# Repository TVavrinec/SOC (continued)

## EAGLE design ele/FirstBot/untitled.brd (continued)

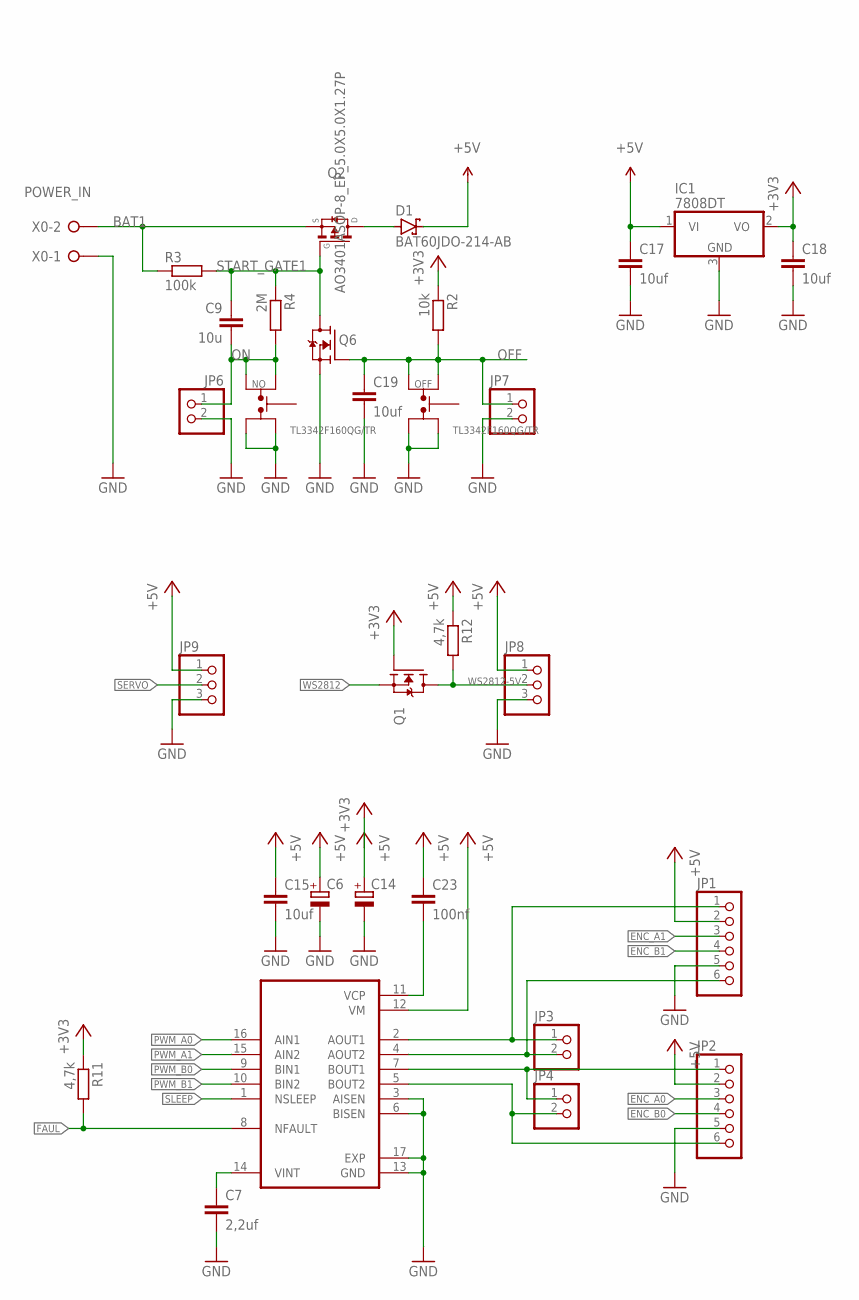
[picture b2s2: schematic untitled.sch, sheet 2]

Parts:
C6, C14: CPOL-EUSANYO_SMD_F8; SANYO-OSCON_SMD_F8
C7: 2,2uf; C0402K
C9: 10u; C0402K
C15, C17, C18: 10uf; C0603
C19: 10uf; C0402K
C23: 100nf; C0402K
D1: BAT60JDO-214-AB; DO214BA
IC1: 7808DT; TO252
JP1, JP2: PINHD-1X6; 1X06
JP3, JP4, JP6, JP7: PINHD-1X2; 1X02
JP8, JP9: PINHD-1X3; 1X03
NO: TL3342F160QG/TR
OFF: TL3342F160QG/TR
Q1, Q6: N-MOSFET-SOT23-GSD; SOT23
Q2: AO3401ASOP-8_EP_5.0X5.0X1.27P; SOP-8_EP_5.0X5.0X1.27P
R2: 10k; R0402
R3: 100k; R0402
R4: 2M; R0402
R11, R12: 4,7k; R0402
U$9: DRV8833CPWPR; SOP65P640X120-17N
X0: POWER_IN; W237-132

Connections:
+3V3: C18.1, IC1.2 (VO), Q1.1 (G), R2.1, R11.1; also elsewhere on the board
+5V: C6.+, C14.+, C15.1, C17.1, C23.2, D1.C, IC1.1 (VI), JP1.2, JP2.2, JP8.1, JP9.1, R12.1, U$9.12 (VM)
BAT1: Q2.1 (S), Q2.2 (S), Q2.3 (S), R3.1, X0.2
ENC_A0: JP2.3; also elsewhere on the board
ENC_A1: JP1.3; also elsewhere on the board
ENC_B0: JP2.4; also elsewhere on the board
ENC_B1: JP1.4; also elsewhere on the board
FAUL: R11.2, U$9.8 (NFAULT); also elsewhere on the board
GND: C6.-, C7.2, C14.-, C15.2, C17.2, C18.2, C19.2, IC1.3 (GND), JP1.5, JP2.5, JP6.2, JP7.2, JP8.3, JP9.3, NO.1, NO.2, OFF.1, OFF.2, Q6.2 (S), U$9.3 (AISEN), U$9.6 (BISEN), U$9.13 (GND), U$9.17 (EXP), X0.1; also elsewhere on the board
unnamed: JP1.1, JP3.1, U$9.2 (AOUT1)
unnamed: D1.A, Q2.5 (D), Q2.6 (D), Q2.7 (D), Q2.8 (D), Q2.9 (D)
unnamed: C23.1, U$9.11 (VCP)
unnamed: JP1.6, JP3.2, U$9.4 (AOUT2)
unnamed: JP2.1, JP4.1, U$9.7 (BOUT1)
unnamed: JP2.6, JP4.2, U$9.5 (BOUT2)
unnamed: C7.1, U$9.14 (VINT)
OFF: C19.1, JP7.1, OFF.3, OFF.4, Q6.1 (G), R2.2
ON: C9.2, JP6.1, NO.3, NO.4, R4.2
PWM_A0: U$9.16 (AIN1); also elsewhere on the board
PWM_A1: U$9.15 (AIN2); also elsewhere on the board
PWM_B0: U$9.9 (BIN1); also elsewhere on the board
PWM_B1: U$9.10 (BIN2); also elsewhere on the board
SERVO: JP9.2; also elsewhere on the board
SLEEP: U$9.1 (NSLEEP); also elsewhere on the board
START_GATE1: C9.1, Q2.4 (G), Q6.3 (D), R3.2, R4.1
WS2812: Q1.2 (S); also elsewhere on the board
WS2812-5V: JP8.2, Q1.3 (D), R12.2

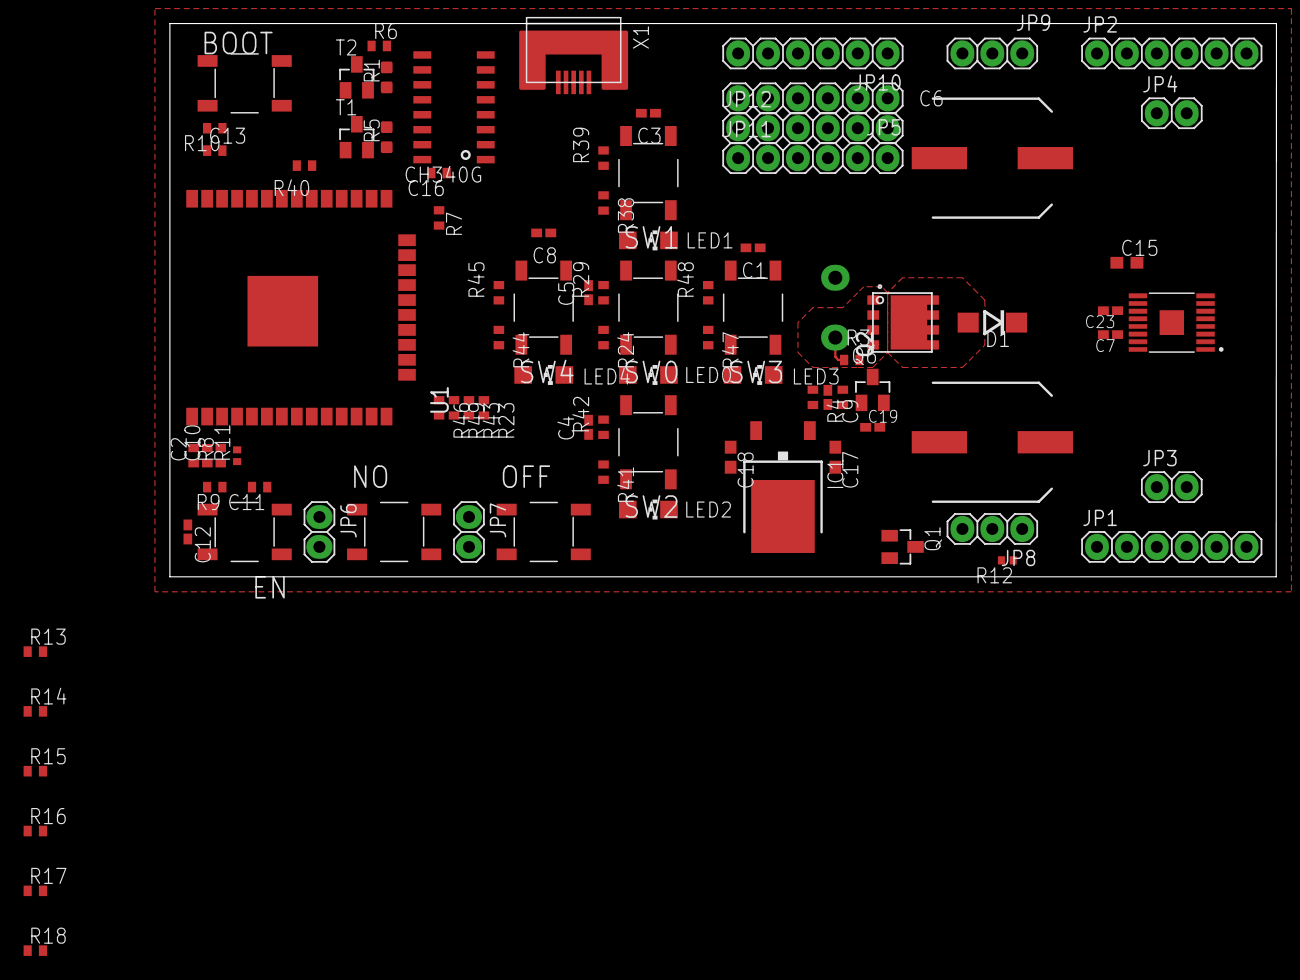
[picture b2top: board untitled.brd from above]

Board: 2 copper layers, 94.0 x 47.0 mm, 91 parts (1 on the bottom side), 61 nets.

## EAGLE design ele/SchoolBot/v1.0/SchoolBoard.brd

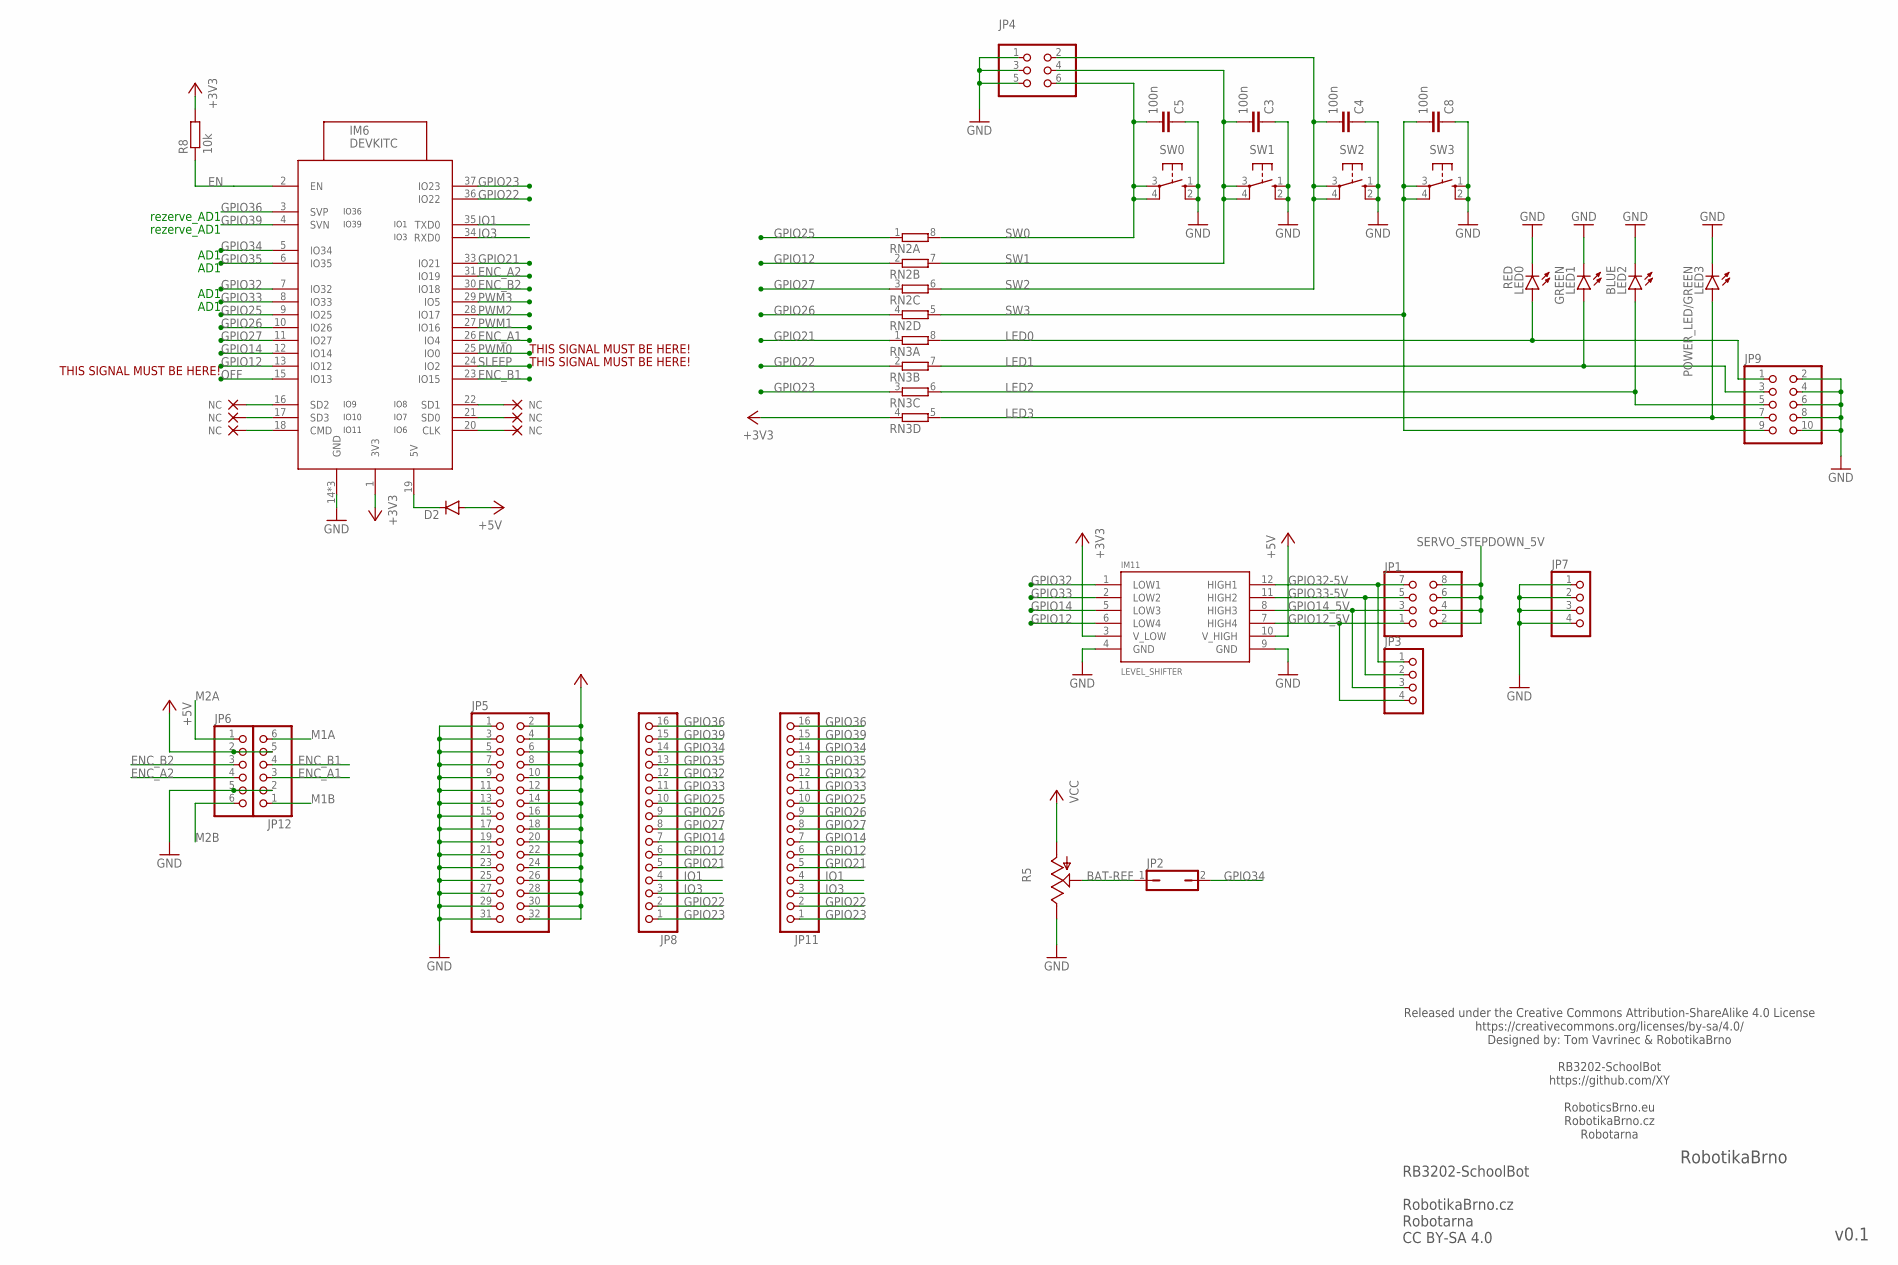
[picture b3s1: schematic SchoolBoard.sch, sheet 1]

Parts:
C3, C4, C5, C8: 100n; C1206
D2: DIODE-D-7.5; D-7.5
IM6: DEVKITC
IM11: LEVEL_SHIFTER
JP1: PINHD-2X4; 2X04
JP2: JP1Q; JP1
JP3, JP7: PINHD-1X4; 1X04
JP4: PINHD-2X3; 2X03
JP5: PINHD-2X16; 2X16
JP6, JP12: PINHD-1X6; 1X06
JP8, JP11: PINHD-1X16; 1X16
JP9: PINHD-2X5; 2X05
LED0: RED; LED3MM
LED1: GREEN; LED3MM
LED2: BLUE; LED3MM
LED3: POWER_LED/GREEN; LED3MM
R5: TRIM_US-SM-42/43X; SM-42/43X
R8: 10k; R0805
RN2, RN3: 4R-NEXBS8V; EXBS8V
SW0, SW1, SW2, SW3: 10-XX; B3F-10XX

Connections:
+3V3: IM6.1 (3V3), IM11.3 (V_LOW), JP5.2, JP5.4, JP5.6, JP5.8, JP5.10, JP5.12, JP5.14, JP5.16, JP5.18, JP5.20, JP5.22, JP5.24, JP5.26, JP5.28, JP5.30, JP5.32, R8.2, RN3.4 (1); also elsewhere on the board
+5V: D2.A, IM11.10 (V_HIGH), JP6.2, JP12.5; also elsewhere on the board
+5V_ESP: D2.C, IM6.19 (5V)
BAT-REF: JP2.1, R5.2 (S)
EN: IM6.2 (EN), R8.1; also elsewhere on the board
ENC_A1: IM6.26 (IO4), JP12.3
ENC_A2: IM6.31 (IO19), JP6.4
ENC_B1: IM6.23 (IO15), JP12.4
ENC_B2: IM6.30 (IO18), JP6.3
GND: C3.1, C4.1, C5.1, C8.1, IM6.14 (GND), IM6.32 (GND), IM6.38 (GND), IM11.4 (GND), IM11.9 (GND), JP4.1, JP4.3, JP4.5, JP5.1, JP5.3, JP5.5, JP5.7, JP5.9, JP5.11, JP5.13, JP5.15, JP5.17, JP5.19, JP5.21, JP5.23, JP5.25, JP5.27, JP5.29, JP5.31, JP6.5, JP7.1, JP7.2, JP7.3, JP7.4, JP9.2, JP9.4, JP9.6, JP9.8, JP9.10, JP12.2, LED0.K (C), LED1.K (C), LED2.K (C), LED3.K (C), R5.3 (E), SW0.1 (S), SW0.2 (S1), SW1.1 (S), SW1.2 (S1), SW2.1 (S), SW2.2 (S1), SW3.1 (S), SW3.2 (S1); also elsewhere on the board
GPIO12: IM6.13 (IO12), IM11.6 (LOW4), JP8.6, JP11.6, RN2.2 (1)
GPIO12_5V: IM11.7 (HIGH4), JP1.1, JP3.4
GPIO14: IM6.12 (IO14), IM11.5 (LOW3), JP8.7, JP11.7
GPIO14_5V: IM11.8 (HIGH3), JP1.3, JP3.3
GPIO21: IM6.33 (IO21), JP8.5, JP11.5, RN3.1
GPIO22: IM6.36 (IO22), JP8.2, JP11.2, RN3.2 (1)
GPIO23: IM6.37 (IO23), JP8.1, JP11.1, RN3.3 (1)
GPIO25: IM6.9 (IO25), JP8.10, JP11.10, RN2.1
GPIO26: IM6.10 (IO26), JP8.9, JP11.9, RN2.4 (1)
GPIO27: IM6.11 (IO27), JP8.8, JP11.8, RN2.3 (1)
GPIO32: IM6.7 (IO32), IM11.1 (LOW1), JP8.12, JP11.12
GPIO32-5V: IM11.12 (HIGH1), JP1.7, JP3.1
GPIO33: IM6.8 (IO33), IM11.2 (LOW2), JP8.11, JP11.11
GPIO33-5V: IM11.11 (HIGH2), JP1.5, JP3.2
GPIO34: IM6.5 (IO34), JP2.2, JP8.14, JP11.14
GPIO35: IM6.6 (IO35), JP8.13, JP11.13; also elsewhere on the board
GPIO36: IM6.3 (SVP), JP8.16, JP11.16
GPIO39: IM6.4 (SVN), JP8.15, JP11.15
IO1: IM6.35 (TXD0), JP8.4, JP11.4
IO3: IM6.34 (RXD0), JP8.3, JP11.3
IO9_NC: IM6.16 (SD2)
IO9_NC1: IM6.20 (CLK)
IO10_NC: IM6.17 (SD3)
IO10_NC1: IM6.21 (SD0)
IO11_NC: IM6.18 (CMD)
IO11_NC1: IM6.22 (SD1)
LED0: JP9.1, LED0.A, RN3.8 (2)
LED1: JP9.3, LED1.A, RN3.7 (2)
LED2: JP9.5, LED2.A, RN3.6 (2)
LED3: JP9.7, LED3.A, RN3.5 (2)
M1A: JP12.6; also elsewhere on the board
M1B: JP12.1; also elsewhere on the board
M2A: JP6.1; also elsewhere on the board
M2B: JP6.6; also elsewhere on the board
OFF: IM6.15 (IO13); also elsewhere on the board
PWM0: IM6.25 (IO0); also elsewhere on the board
PWM1: IM6.27 (IO16); also elsewhere on the board
PWM2: IM6.28 (IO17); also elsewhere on the board
PWM3: IM6.29 (IO5); also elsewhere on the board
SERVO_STEPDOWN_5V: JP1.2, JP1.4, JP1.6, JP1.8; also elsewhere on the board
SLEEP: IM6.24 (IO2); also elsewhere on the board
SW0: C5.2, JP4.6, RN2.8 (2), SW0.3, SW0.4 (P1)
SW1: C3.2, JP4.4, RN2.7 (2), SW1.3, SW1.4 (P1)
SW2: C4.2, JP4.2, RN2.6 (2), SW2.3, SW2.4 (P1)
SW3: C8.2, JP9.9, RN2.5 (2), SW3.3, SW3.4 (P1)
VCC: R5.1 (A); also elsewhere on the board

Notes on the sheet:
AD1
rezerve_AD1
RB3202-SchoolBot RobotikaBrno.cz Robotarna CC BY-SA 4.0
RobotikaBrno
v0.1
Released under the Creative Commons Attribution-ShareAlike 4.0 License https://creativecommons.org/licenses/by-sa/4.0/ Designed by: Tom Vavrinec & RobotikaBrno RB3202-SchoolBot https://github.com/XY RoboticsBrno.eu RobotikaBrno.cz Robotarna
THIS SIGNAL MUST BE HERE!

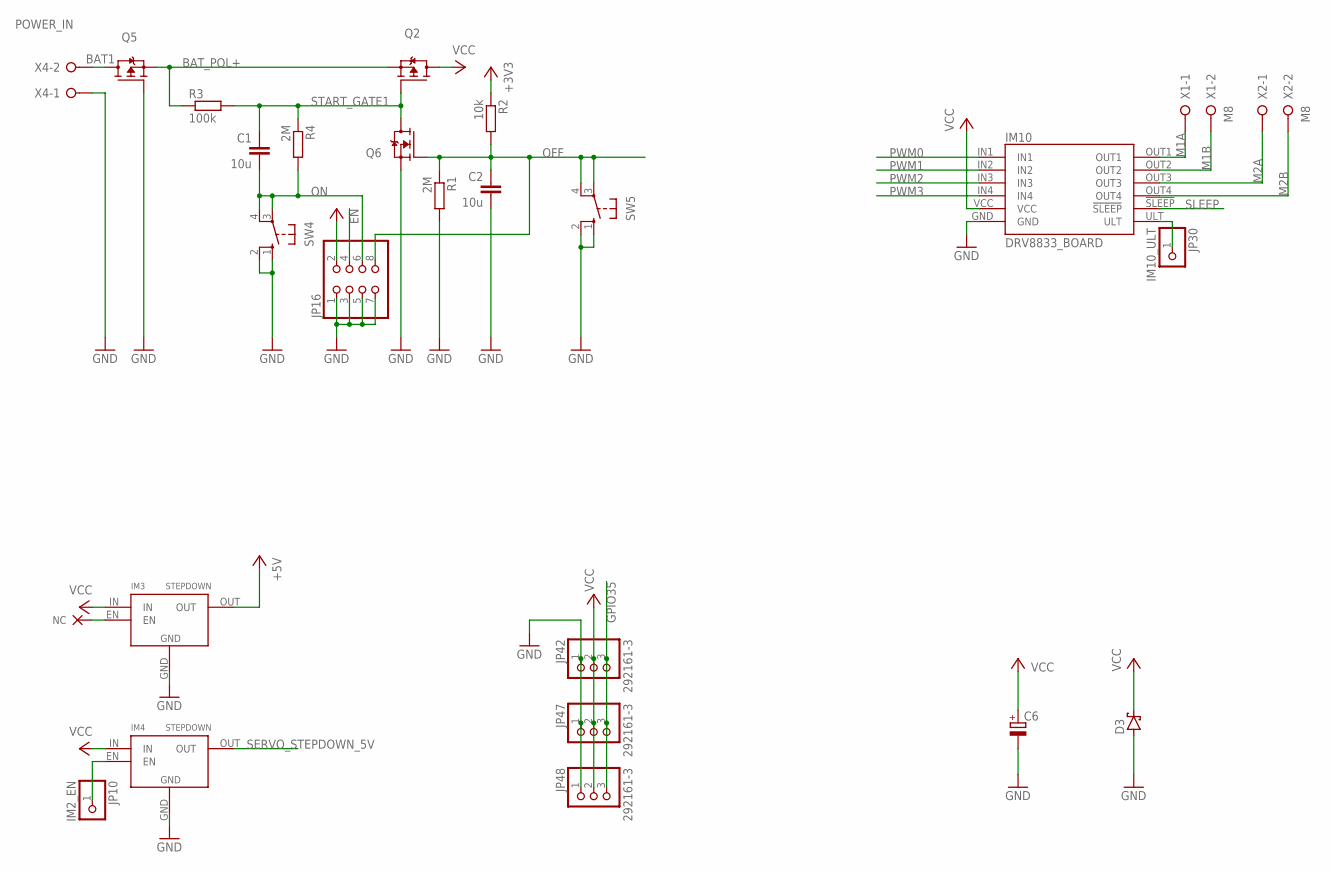
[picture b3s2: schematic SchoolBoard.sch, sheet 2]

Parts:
C1, C2: 10u; C1206
C6: CPOL-EUE5-10.5; E5-10,5
D3: SCHOTTKY-DIODEF126Z12; F126Z12
IM3, IM4: STEPDOWN
IM10: DRV8833_BOARD; PINHEAD
JP10: IM2_EN; 1X01
JP16: PINHD-2X4; 2X04
JP30: IM10_ULT; 1X01
JP42, JP47, JP48: 292161-3
Q2, Q5: P-MOSFET-TO220V; TO220V
Q6: N-MOSFET-SOT23-GSD; SOT23
R1: 2M; R0805
R2: 10k; R0805
R3: 100k; R0805
R4: 2M; M0805
SW4, SW5: 10-XX; B3F-10XX
X1, X2: M8; W237-132
X4: POWER_IN; W237-132

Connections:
+3V3: R2.1; also elsewhere on the board
+5V: IM3.OUT, JP16.2; also elsewhere on the board
BAT1: Q5.2 (D), X4.2
BAT_POL+: Q2.3 (S), Q5.3 (S), R3.1
EN: JP16.4; also elsewhere on the board
GND: C2.2, C6.-, D3.A, IM3.GND, IM4.GND, IM10.GND, JP16.1, JP16.3, JP16.5, JP16.7, JP42.1, JP47.1, JP48.1, Q5.1 (G), Q6.2 (S), R1.2, SW4.1 (S), SW4.2 (S1), SW5.1 (S), SW5.2 (S1), X4.1; also elsewhere on the board
GPIO35: JP42.3, JP47.3, JP48.3; also elsewhere on the board
IO9_NC2: IM3.EN
M1A: IM10.OUT1, X1.1; also elsewhere on the board
M1B: IM10.OUT2, X1.2; also elsewhere on the board
M2A: IM10.OUT3, X2.1; also elsewhere on the board
M2B: IM10.OUT4, X2.2; also elsewhere on the board
unnamed: IM10.ULT, JP30.1
OFF: C2.1, JP16.8, Q6.1 (G), R1.1, R2.2, SW5.3, SW5.4 (P1); also elsewhere on the board
ON: C1.2, JP16.6, R4.2, SW4.3, SW4.4 (P1)
PWM0: IM10.IN1; also elsewhere on the board
PWM1: IM10.IN2; also elsewhere on the board
PWM2: IM10.IN3; also elsewhere on the board
PWM3: IM10.IN4; also elsewhere on the board
SERVO_STEPDOWN_5V: IM4.OUT; also elsewhere on the board
SLEEP: IM10.!SLEEP; also elsewhere on the board
START_GATE1: C1.1, Q2.1 (G), Q6.3 (D), R3.2, R4.1
STEP2_EN1: IM4.EN, JP10.1
VCC: C6.+, D3.C, IM3.IN, IM4.IN, IM10.VCC, JP42.2, JP47.2, JP48.2, Q2.2 (D); also elsewhere on the board

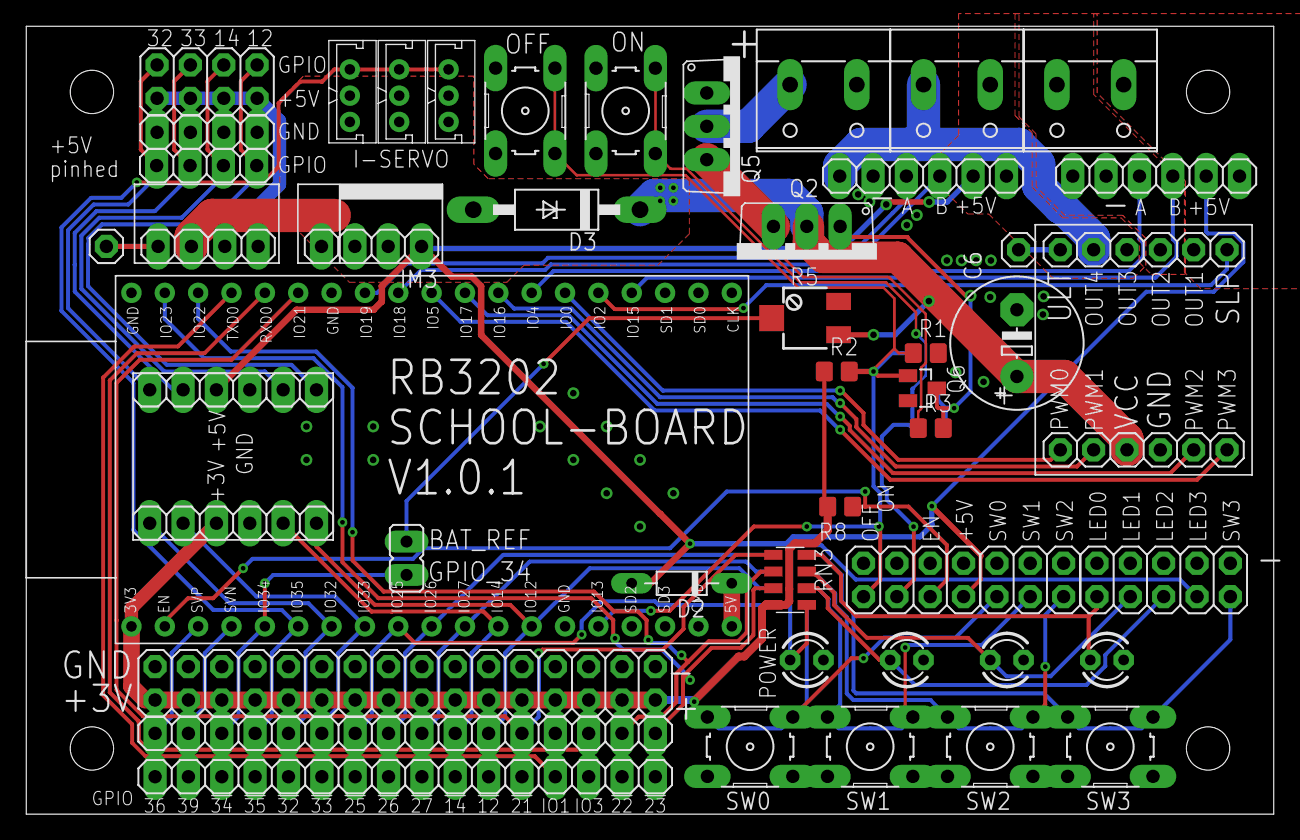
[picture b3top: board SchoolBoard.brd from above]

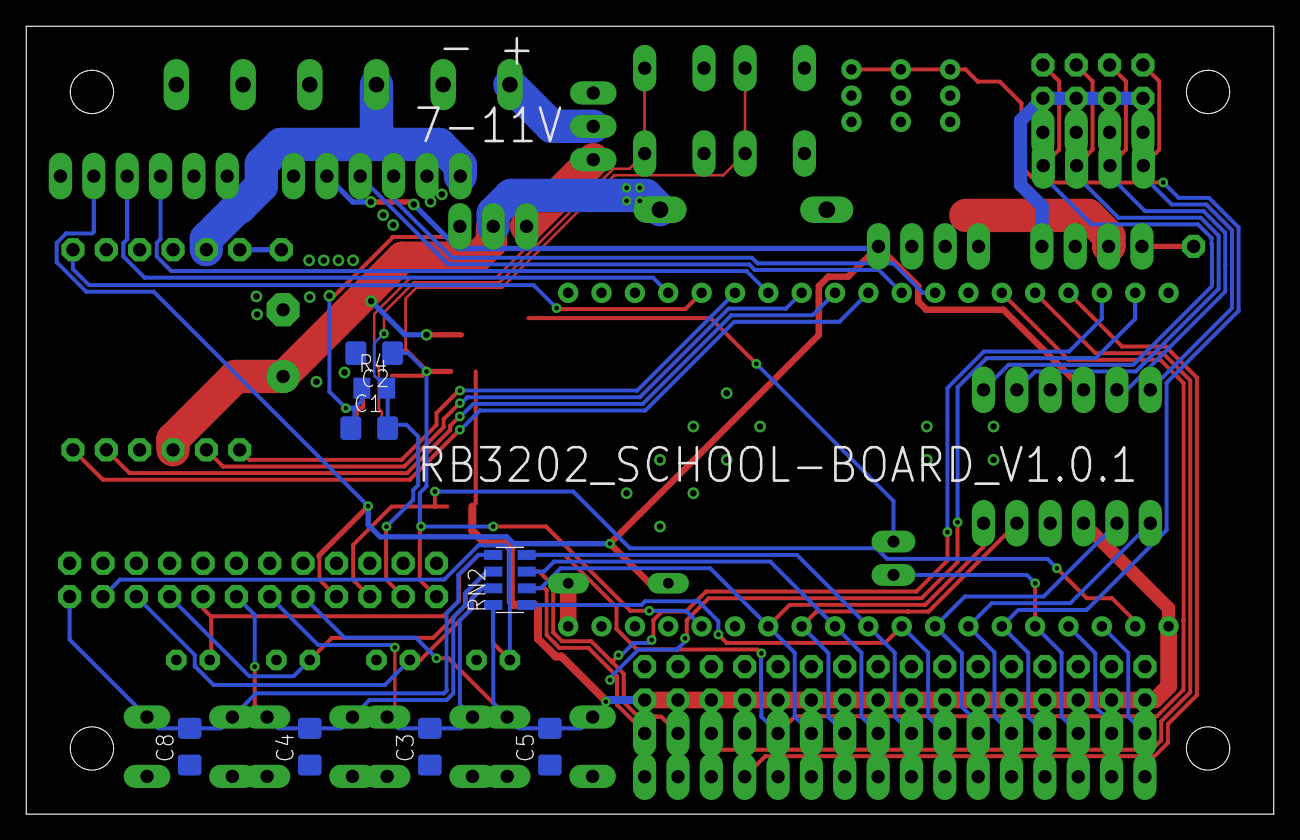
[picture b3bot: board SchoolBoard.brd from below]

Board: 2 copper layers, 95.0 x 60.0 mm, 55 parts (8 on the bottom side), 56 nets.

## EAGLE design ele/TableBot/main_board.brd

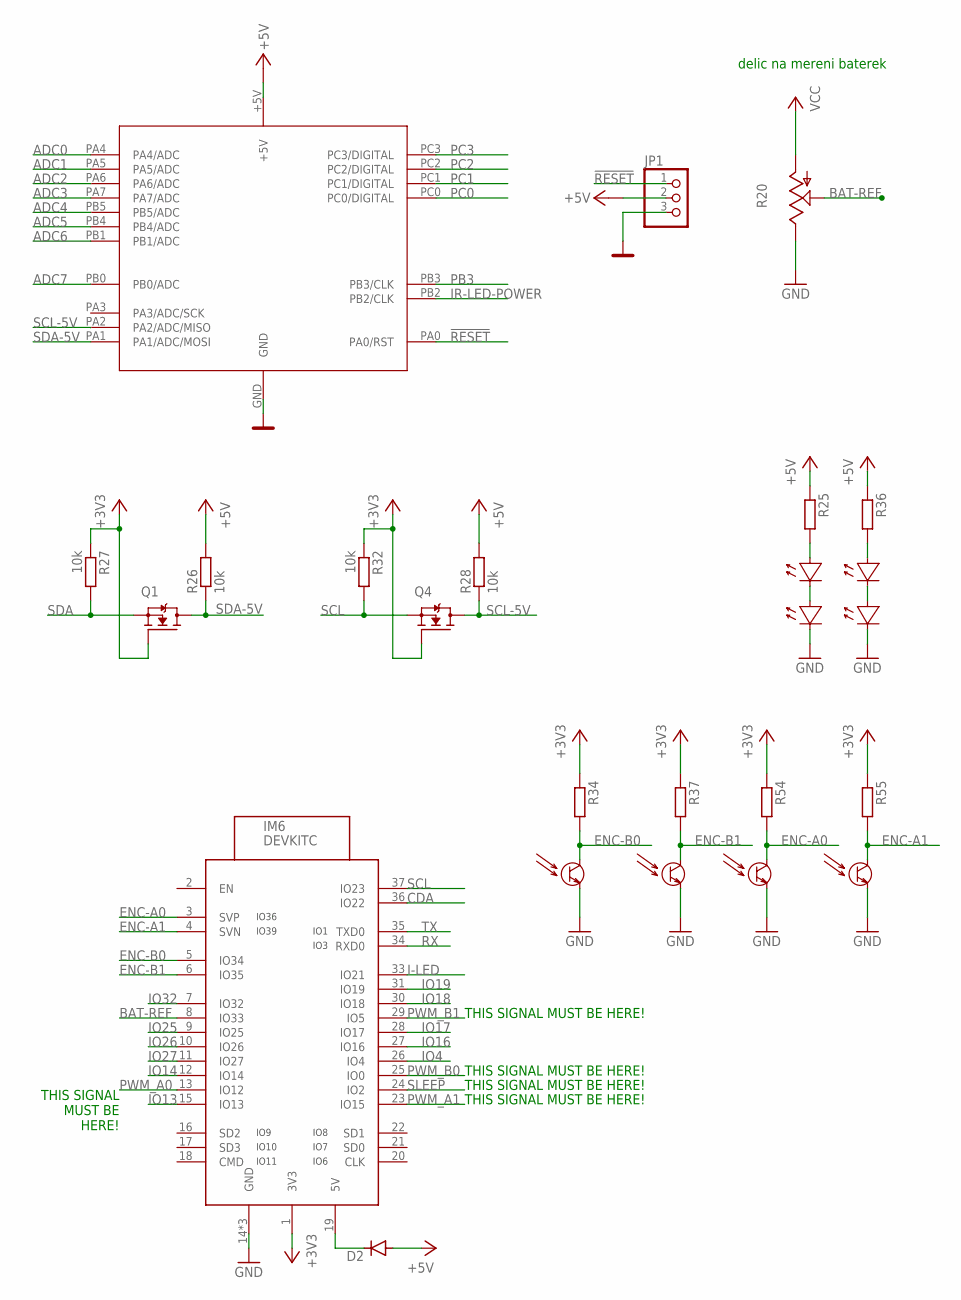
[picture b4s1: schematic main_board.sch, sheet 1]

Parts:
D2: DIODE-D-7.5; D-7.5
IM6: DEVKITC
JP1: PINHD-1X3; 1X03
Q1, Q4: N-MOSFET-SOT23-DIST; SOT23_DIST
R20: TRIM_US-SM-42/43X; SM-42/43X
R25, R34, R36, R37, R54, R55: R-EU_R0603; R0603
R26, R27, R28, R32: 10k; R0402
U$8: ATTINI1616SOIC; ATTINY1616-SOIC
U$11, U$15, U$16, U$20: BIR-NM13C1
U$13, U$21, U$22, U$23: L-NP-3C1

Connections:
!RESET: JP1.1, U$8.PA0 (PA0/RST)
+3V3: IM6.1 (3V3), Q1.1 (G), Q4.1 (G), R27.1, R32.1, R34.1, R37.1, R54.1, R55.1; also elsewhere on the board
+5V: D2.A, JP1.2, R25.1, R26.2, R28.2, R36.1, U$8.+5V; also elsewhere on the board
+5V_ESP: D2.C, IM6.19 (5V)
ADC0: U$8.PA4 (PA4/ADC); also elsewhere on the board
ADC1: U$8.PA5 (PA5/ADC); also elsewhere on the board
ADC2: U$8.PA6 (PA6/ADC); also elsewhere on the board
ADC3: U$8.PA7 (PA7/ADC); also elsewhere on the board
ADC4: U$8.PB5 (PB5/ADC); also elsewhere on the board
ADC5: U$8.PB4 (PB4/ADC); also elsewhere on the board
ADC6: U$8.PB1 (PB1/ADC); also elsewhere on the board
ADC7: U$8.PB0 (PB0/ADC)
BAT-REF: IM6.8 (IO33), R20.2 (S)
CDA: IM6.36 (IO22)
ENC-A0: IM6.3 (SVP), R54.2, U$22.PIN
ENC-A1: IM6.4 (SVN), R55.2, U$23.PIN
ENC-B0: IM6.5 (IO34), R34.2, U$13.PIN
ENC-B1: IM6.6 (IO35), R37.2, U$21.PIN
GND: IM6.14 (GND), IM6.32 (GND), IM6.38 (GND), JP1.3, R20.3 (E), U$8.GND, U$11.GND, U$13.GND, U$20.GND, U$21.GND, U$22.GND, U$23.GND; also elsewhere on the board
I-LED: IM6.33 (IO21); also elsewhere on the board
IO4: IM6.26 (IO4); also elsewhere on the board
IO13: IM6.15 (IO13); also elsewhere on the board
IO14: IM6.12 (IO14); also elsewhere on the board
IO16: IM6.27 (IO16); also elsewhere on the board
IO17: IM6.28 (IO17); also elsewhere on the board
IO18: IM6.30 (IO18); also elsewhere on the board
IO19: IM6.31 (IO19); also elsewhere on the board
IO25: IM6.9 (IO25); also elsewhere on the board
IO26: IM6.10 (IO26); also elsewhere on the board
IO27: IM6.11 (IO27); also elsewhere on the board
IO32: IM6.7 (IO32); also elsewhere on the board
IR-LED-POWER: U$8.PB2 (PB2/CLK); also elsewhere on the board
unnamed: R25.2, U$16.PIN (VCC)
unnamed: U$11.PIN (VCC), U$16.GND
unnamed: R36.2, U$15.PIN (VCC)
unnamed: U$15.GND, U$20.PIN (VCC)
PB3: U$8.PB3 (PB3/CLK); also elsewhere on the board
PC0: U$8.PC0 (PC0/DIGITAL); also elsewhere on the board
PC1: U$8.PC1 (PC1/DIGITAL); also elsewhere on the board
PC2: U$8.PC2 (PC2/DIGITAL); also elsewhere on the board
PC3: U$8.PC3 (PC3/DIGITAL)
PWM_A0: IM6.13 (IO12); also elsewhere on the board
PWM_A1: IM6.23 (IO15); also elsewhere on the board
PWM_B0: IM6.25 (IO0); also elsewhere on the board
PWM_B1: IM6.29 (IO5); also elsewhere on the board
RX: IM6.34 (RXD0); also elsewhere on the board
SCL: IM6.37 (IO23), Q4.2 (S), R32.2
SCL-5V: Q4.3 (D), R28.1, U$8.PA2 (PA2/ADC/MISO)
SDA: Q1.2 (S), R27.2
SDA-5V: Q1.3 (D), R26.1, U$8.PA1 (PA1/ADC/MOSI)
SLEEP: IM6.24 (IO2); also elsewhere on the board
TX: IM6.35 (TXD0); also elsewhere on the board
VCC: R20.1 (A); also elsewhere on the board

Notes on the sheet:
delic na mereni baterek
THIS SIGNAL MUST BE HERE!
THIS SIGNAL MUST BE HERE!

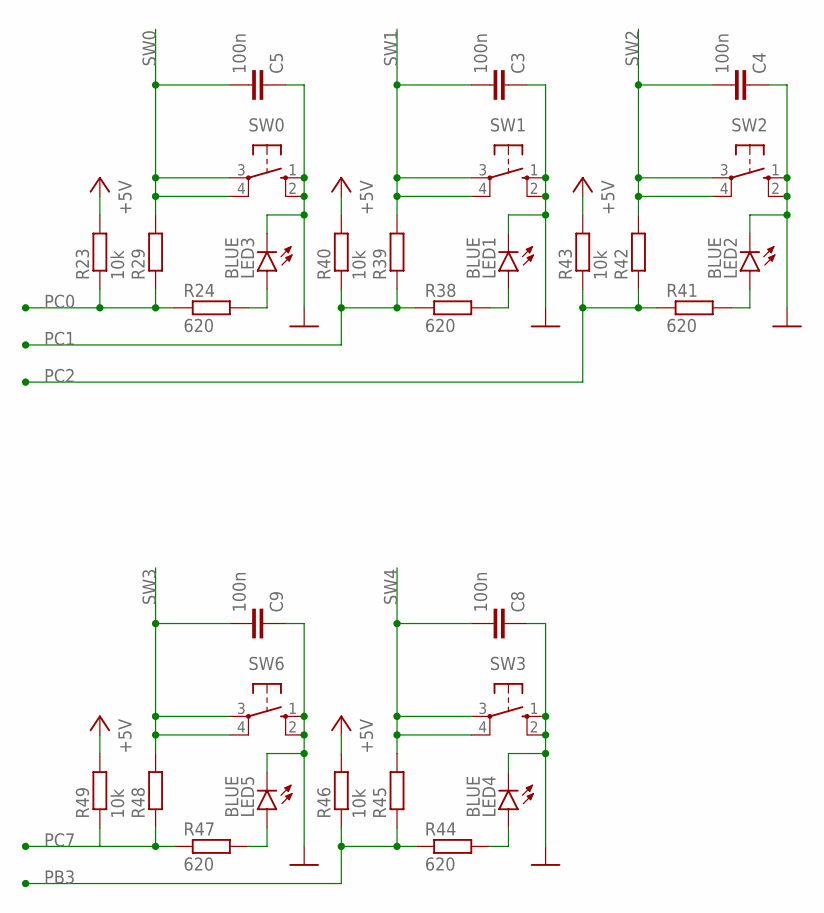
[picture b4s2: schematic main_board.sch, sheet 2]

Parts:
C3, C4, C5, C8, C9: 100n; C1206
LED1, LED2, LED3, LED4, LED5: BLUE; CHIPLED_1206
R23, R40, R43, R46, R49: 10k; R0805
R24, R38, R41, R44, R47: 620; R0805
R29, R39, R42, R45, R48: R-EU_R0805; R0805
SW0, SW1, SW2, SW3, SW6: 10-XX; B3F-10XX

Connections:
+5V: R23.2, R40.2, R43.2, R46.2, R49.2; also elsewhere on the board
GND: C3.1, C4.1, C5.1, C8.1, C9.1, LED1.C, LED2.C, LED3.C, LED4.C, LED5.C, SW0.1 (S), SW0.2 (S1), SW1.1 (S), SW1.2 (S1), SW2.1 (S), SW2.2 (S1), SW3.1 (S), SW3.2 (S1), SW6.1 (S), SW6.2 (S1); also elsewhere on the board
unnamed: LED3.A, R24.2
unnamed: LED2.A, R41.2
unnamed: LED1.A, R38.2
unnamed: LED4.A, R44.2
unnamed: LED5.A, R47.2
PB3: R44.1, R45.1, R46.1; also elsewhere on the board
PC0: R23.1, R24.1, R29.1; also elsewhere on the board
PC1: R38.1, R39.1, R40.1; also elsewhere on the board
PC2: R41.1, R42.1, R43.1; also elsewhere on the board
PC7: R47.1, R48.1, R49.1
SW0: C5.2, R29.2, SW0.3, SW0.4 (P1); also elsewhere on the board
SW1: C3.2, R39.2, SW1.3, SW1.4 (P1); also elsewhere on the board
SW2: C4.2, R42.2, SW2.3, SW2.4 (P1); also elsewhere on the board
SW3: C9.2, R48.2, SW6.3, SW6.4 (P1); also elsewhere on the board
SW4: C8.2, R45.2, SW3.3, SW3.4 (P1); also elsewhere on the board

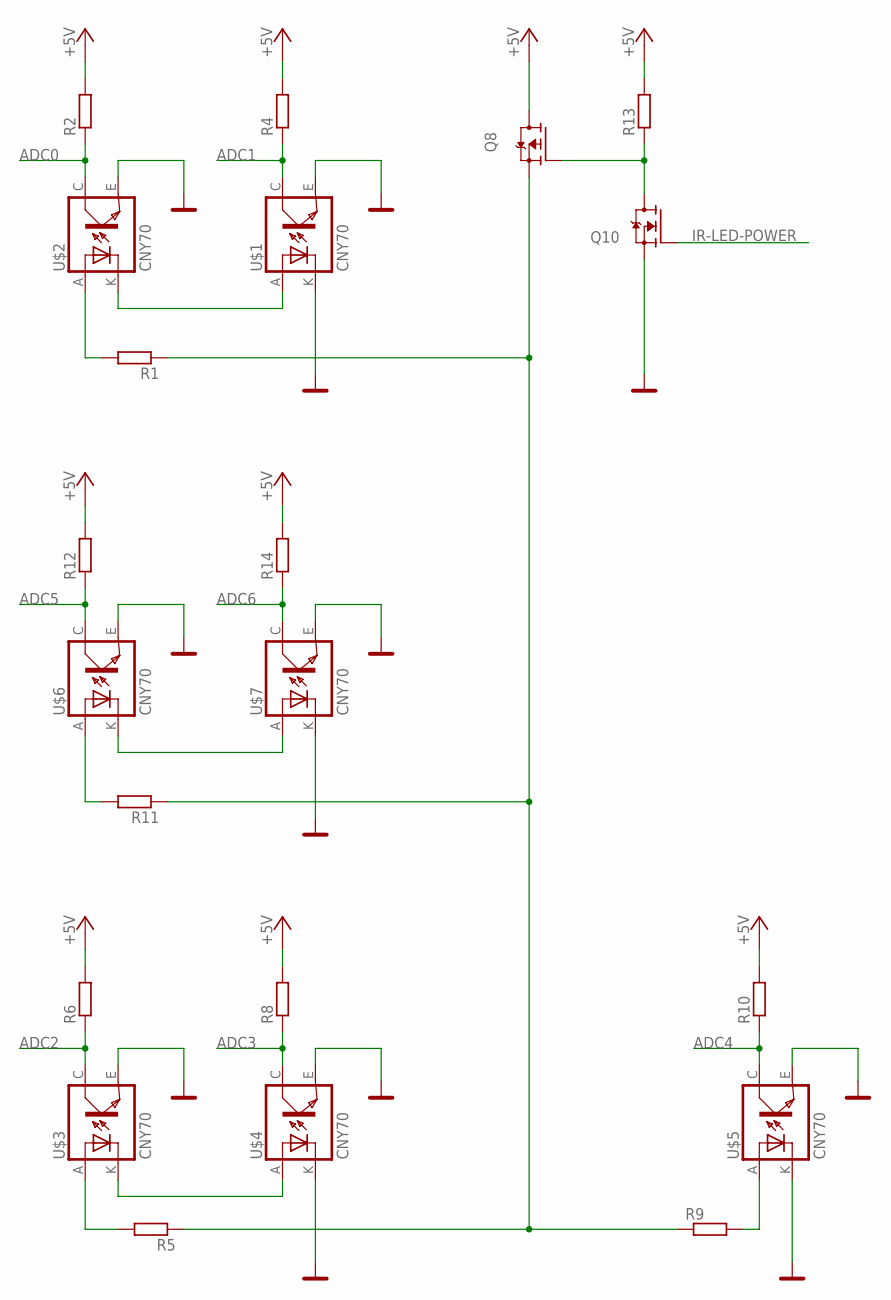
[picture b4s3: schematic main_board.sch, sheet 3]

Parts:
Q8: P-MOSFET-MLP_HS; MLP3.3X3.3_HS
Q10: N-MOSFET-SOT23-GSD; SOT23
R1, R2, R4, R5, R6, R8, R9, R10, R11, R12, R13, R14: R-EU_R0603; R0603
U$1, U$2, U$3, U$4, U$5, U$6, U$7: CNY70; 4

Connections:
+5V: Q8.5 (D), Q8.6 (D), Q8.7 (D), Q8.8 (D), R2.2, R4.2, R6.2, R8.2, R10.2, R12.2, R13.2, R14.2; also elsewhere on the board
ADC0: R2.1, U$2.C (COL); also elsewhere on the board
ADC1: R4.1, U$1.C (COL); also elsewhere on the board
ADC2: R6.1, U$3.C (COL); also elsewhere on the board
ADC3: R8.1, U$4.C (COL); also elsewhere on the board
ADC4: R10.1, U$5.C (COL); also elsewhere on the board
ADC5: R12.1, U$6.C (COL); also elsewhere on the board
ADC6: R14.1, U$7.C (COL); also elsewhere on the board
GND: Q10.2 (S), U$1.E (EMI), U$1.K (C), U$2.E (EMI), U$3.E (EMI), U$4.E (EMI), U$4.K (C), U$5.E (EMI), U$5.K (C), U$6.E (EMI), U$7.E (EMI), U$7.K (C); also elsewhere on the board
IR-LED-POWER: Q10.1 (G); also elsewhere on the board
unnamed: R1.2, U$2.A
unnamed: U$1.A, U$2.K (C)
unnamed: R5.2, U$3.A
unnamed: U$3.K (C), U$4.A
unnamed: R9.2, U$5.A
unnamed: R11.2, U$6.A
unnamed: U$6.K (C), U$7.A
unnamed: Q8.1 (S), Q8.2 (S), Q8.3 (S), R1.1, R5.1, R9.1, R11.1
unnamed: Q8.4 (G), Q10.3 (D), R13.1

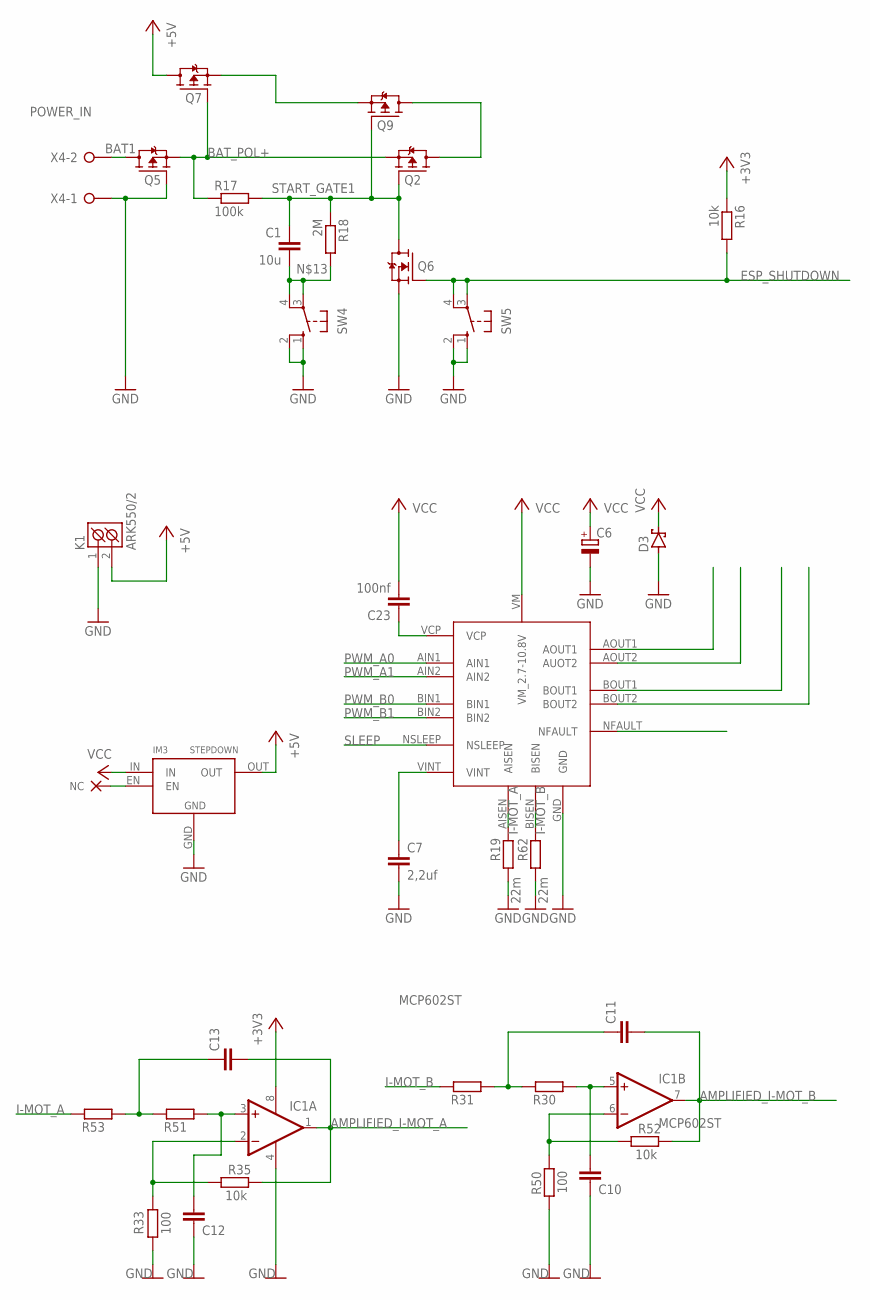
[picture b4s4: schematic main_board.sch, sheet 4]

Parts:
C1: 10u; C1206
C6: CPOL-EUE5-10.5; E5-10,5
C7: 2,2uf; C0805
C10, C11, C12, C13: C-EUC1206; C1206
C23: 100nf; C0603
D3: SCHOTTKY-DIODEF126Z12; F126Z12
IC1: MCP602ST; TSSOP8
IM3: STEPDOWN
K1: ARK550/2
Q2, Q5, Q7, Q9: P-MOSFET-MLP_HS; MLP3.3X3.3_HS
Q6: N-MOSFET-SOT23-GSD; SOT23
R16: 10k; R0805
R17: 100k; R0805
R18: 2M; M0805
R19, R62: 22m; R0603
R30, R31, R51, R53: R-EU_R0603; R0603
R33, R50: 100; R0603
R35, R52: 10k; R0603
SW4, SW5: 10-XX; B3F-10XX
U$9: DRV8833HTSSOP; HTSSOP
X4: POWER_IN; W237-132

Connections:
+3V3: IC1.8 (V+), R16.1; also elsewhere on the board
+5V: IM3.OUT, K1.2 (K2), Q7.5 (D), Q7.6 (D), Q7.7 (D), Q7.8 (D); also elsewhere on the board
AMPLIFIED_I-MOT_A: C13.2, IC1.1 (OUT), R35.2
AMPLIFIED_I-MOT_B: C11.2, IC1.7 (OUT), R52.2
BAT1: Q5.5 (D), Q5.6 (D), Q5.7 (D), Q5.8 (D), X4.2
BAT_POL+: Q2.1 (S), Q2.2 (S), Q2.3 (S), Q5.1 (S), Q5.2 (S), Q5.3 (S), Q7.4 (G), R17.1
ESP_SHUTDOWN: Q6.1 (G), R16.2, SW5.3, SW5.4 (P1)
GND: C6.-, C7.2, C10.2, C12.2, D3.A, IC1.4 (V-), IM3.GND, K1.1 (K1), Q5.4 (G), Q6.2 (S), R19.1, R33.1, R50.1, R62.1, SW4.1 (S), SW4.2 (S1), SW5.1 (S), SW5.2 (S1), U$9.GND, X4.1; also elsewhere on the board
I-MOT_A: R19.2, R53.2, U$9.AISEN
I-MOT_B: R31.2, R62.2, U$9.BISEN
IO9_NC2: IM3.EN
unnamed: Q2.5 (D), Q2.6 (D), Q2.7 (D), Q2.8 (D), Q9.5 (D), Q9.6 (D), Q9.7 (D), Q9.8 (D)
unnamed: Q7.1 (S), Q7.2 (S), Q7.3 (S), Q9.1 (S), Q9.2 (S), Q9.3 (S)
unnamed: C1.2, R18.2, SW4.3, SW4.4 (P1)
unnamed: C11.1, R30.2, R31.1
unnamed: C10.1, IC1.5 (+IN), R30.1
unnamed: IC1.2 (-IN), R33.2, R35.1
unnamed: C7.1, U$9.VINT
unnamed: C23.1, U$9.VCP
unnamed: IC1.6 (-IN), R50.2, R52.1
unnamed: C13.1, R51.2, R53.1
unnamed: C12.1, IC1.3 (+IN), R51.1
PWM_A0: U$9.AIN1; also elsewhere on the board
PWM_A1: U$9.AIN2; also elsewhere on the board
PWM_B0: U$9.BIN1; also elsewhere on the board
PWM_B1: U$9.BIN2; also elsewhere on the board
SLEEP: U$9.NSLEEP; also elsewhere on the board
START_GATE1: C1.1, Q2.4 (G), Q6.3 (D), Q9.4 (G), R17.2, R18.1
VCC: C6.+, C23.2, D3.C, IM3.IN, U$9.VM (VM_2.7-10.8V); also elsewhere on the board
